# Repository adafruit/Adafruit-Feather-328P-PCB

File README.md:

## Adafruit Feather 328P PCB

<a href="http://www.adafruit.com/products/3458"><br/>
Click here to purchase one from the Adafruit shop</a>

PCB files for the Adafruit Feather 328P. Format is EagleCAD schematic and board layout

For more details, check out the product page at
* https://www.adafruit.com/product/3458

### Description

With this Feather we're getting a little nostalgic for the ATmega328P - the classic 'Arduino' chip - with this Adafruit Feather 328P running a 3.3V and 8 MHz. Feather is the new development board from Adafruit, and like it's namesake it is thin, light, and lets you fly! We designed Feather to be a new standard for portable microcontroller cores. We have other boards in the Feather family, check'em out here.

At the Feather 328P's heart is an ATmega328P clocked at 8 MHz and at 3.3V logic, a chip setup we've had tons of experience with as it's the same as the Pro Mini and similar to the Adafruit Metro 328. This chip has 32K of flash and 2K of RAM, and we paired it with a SiLabs CP2104 to give it USB-to-Serial program & debug capability built in. Works great when you want to keep your classic Arduino code compatibility, but want to use one of our dozens of FeatherWings

To make it easy to use for portable projects, we added a connector for any of our 3.7V Lithium polymer batteries and built in battery charging. You don't need a battery, it will run just fine straight from the micro USB connector. But, if you do have a battery, you can take it on the go, then plug in the USB to recharge. The Feather will automatically switch over to USB power when its available. We also tied the battery thru a divider to an analog pin, so you can measure and monitor the battery voltage to detect when you need a recharge.

### License

Adafruit invests time and resources providing this open source design, please support Adafruit and open-source hardware by purchasing products from [Adafruit](https://www.adafruit.com)!

Designed by Limor Fried/Ladyada for Adafruit Industries.

Creative Commons Attribution/Share-Alike, all text above must be included in any redistribution. See license.txt for additional details.

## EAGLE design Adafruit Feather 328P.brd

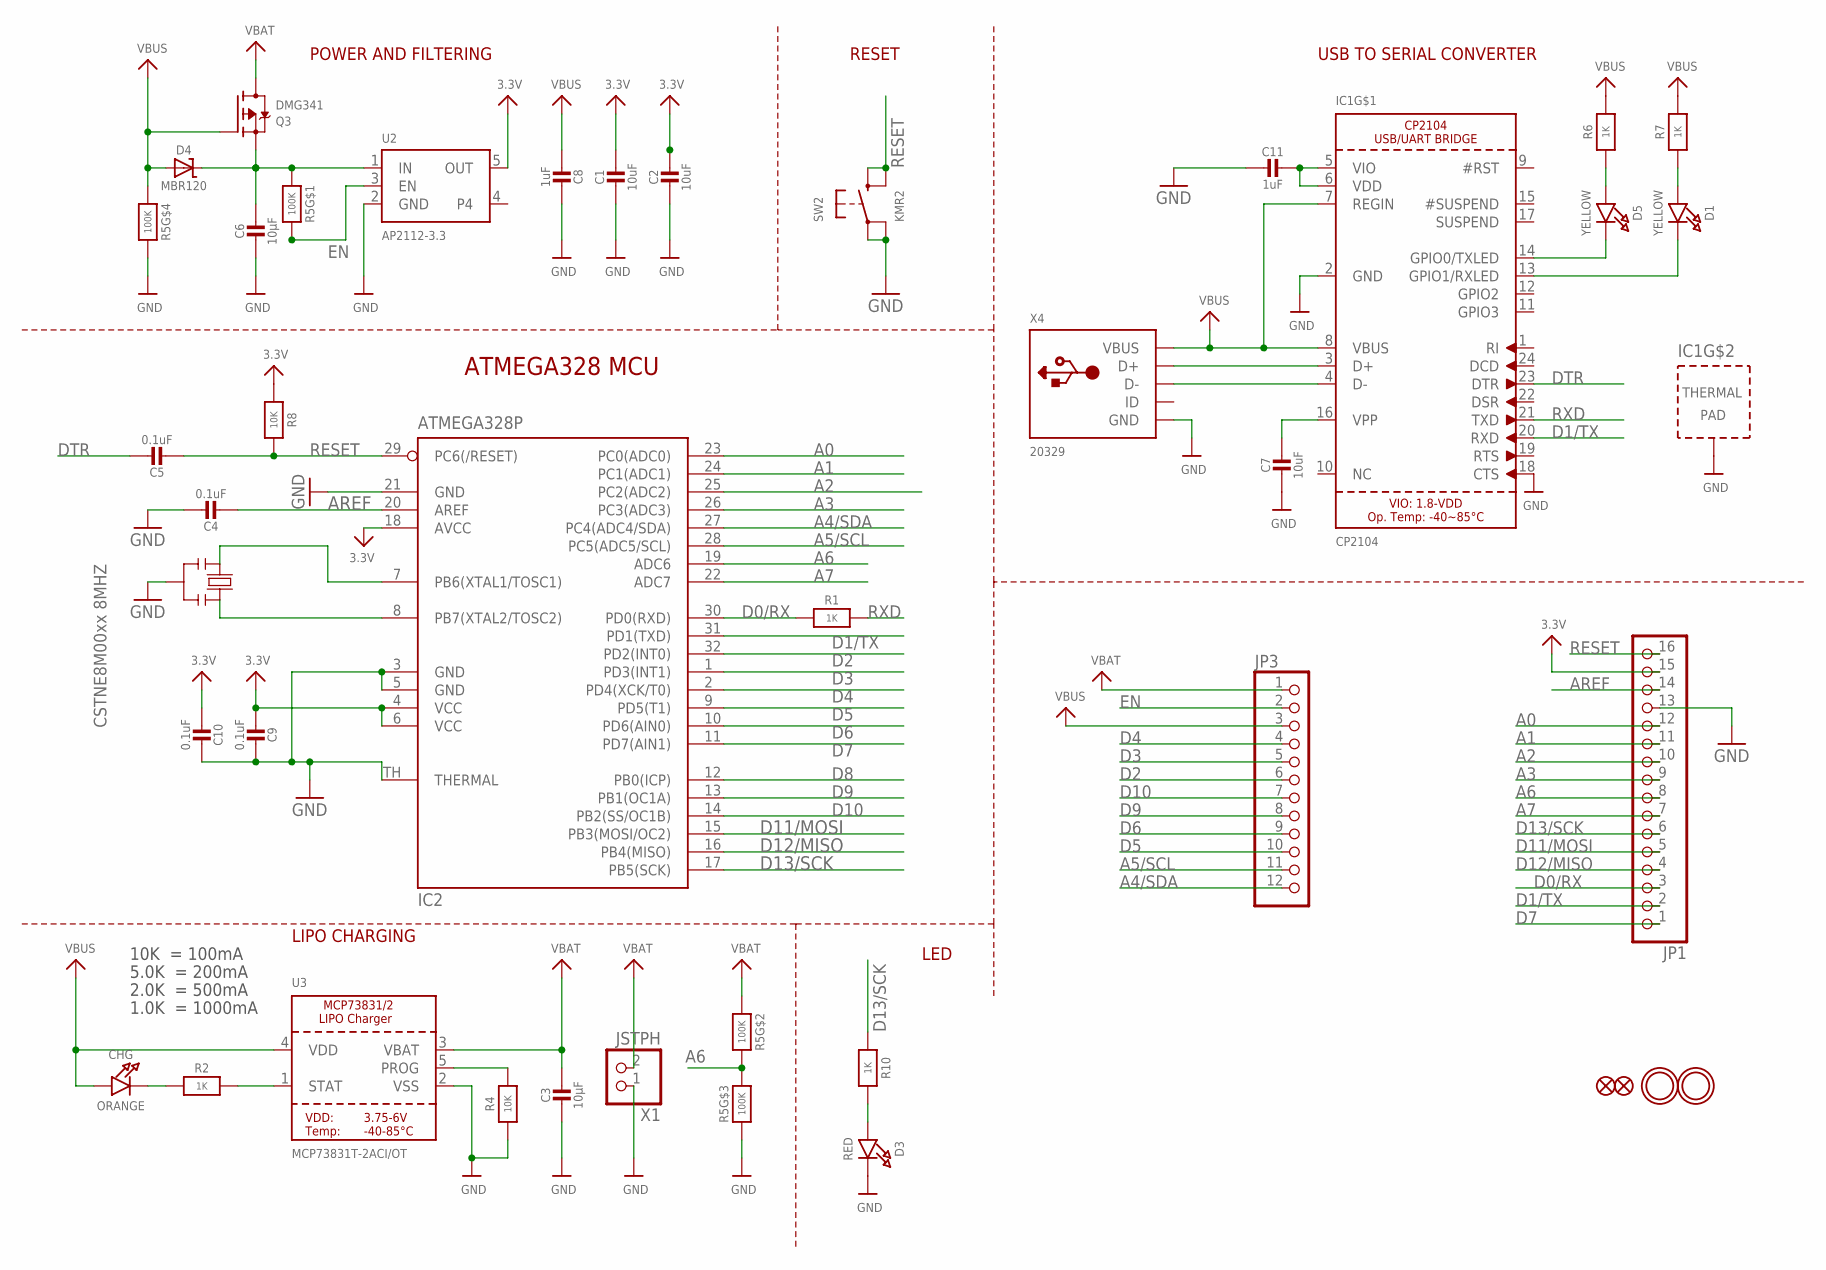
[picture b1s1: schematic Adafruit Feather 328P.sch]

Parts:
C1, C2: 10uF; 0805-NO
C3, C6: 10µF; 0805-NO
C4, C5, C9, C10: 0.1uF; 0603-NO
C7: 10uF; _0805MP
C8, C11: 1uF; 0603-NO
CHG: ORANGE; CHIPLED_0805_NOOUTLINE
D1, D5: YELLOW; CHIPLED_0805_NOOUTLINE
D3: RED; CHIPLED_0805_NOOUTLINE
D4: MBR120; SOD-123
IC1: CP2104; QFN24_4MM_SMSC
IC2: ATMEGA328P; MLF32-TH
JP1: HEADER-1X16ROUND; 1X16_ROUND
JP3: HEADER-1X12; 1X12_ROUND
Q3: DMG341; SOT23-R
R1: 1K; _0603MP
R2, R6, R7, R10: 1K; 0603-NO
R4, R8: 10K; 0603-NO
R5: 100K; RESPACK_4X0603
SW2: KMR2; BTN_KMR2_4.6X2.8
U2: AP2112-3.3; SOT23-5
U3: MCP73831T-2ACI/OT; SOT23-5
U$31, U$32: MOUNTINGHOLE2.5; MOUNTINGHOLE_2.5_PLATED
U$34, U$35: FIDUCIAL_1MM
X1: JSTPH; JSTPH2
X4: 20329; 4UCONN_20329_V2
Y2: CSTNE8M00xx 8MHZ; RESONATOR

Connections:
3.3V: C1.1, C2.1, C9.2, C10.2, IC2.4 (VCC), IC2.6 (VCC), IC2.18 (AVCC), JP1.15, R8.2, U2.5 (OUT)
A0: IC2.23 (PC0(ADC0)), JP1.12
A1: IC2.24 (PC1(ADC1)), JP1.11
A2: IC2.25 (PC2(ADC2)), JP1.10
A3: IC2.26 (PC3(ADC3)), JP1.9
A4/SDA: IC2.27 (PC4(ADC4/SDA)), JP3.12
A5/SCL: IC2.28 (PC5(ADC5/SCL)), JP3.11
A6: IC2.19 (ADC6), JP1.8, R5.6 (2), R5.7 (2)
A7: IC2.22 (ADC7), JP1.7
AREF: C4.2, IC2.20 (AREF), JP1.14
D0/RX: IC2.30 (PD0(RXD)), JP1.3, R1.1
D1/TX: IC1.20 (RXD), IC2.31 (PD1(TXD)), JP1.2
D2: IC2.32 (PD2(INT0)), JP3.6
D3: IC2.1 (PD3(INT1)), JP3.5
D4: IC2.2 (PD4(XCK/T0)), JP3.4
D5: IC2.9 (PD5(T1)), JP3.10
D6: IC2.10 (PD6(AIN0)), JP3.9
D7: IC2.11 (PD7(AIN1)), JP1.1
D8: IC2.12 (PB0(ICP))
D9: IC2.13 (PB1(OC1A)), JP3.8
D10: IC2.14 (PB2(SS/OC1B)), JP3.7
D11/MOSI: IC2.15 (PB3(MOSI/OC2)), JP1.5
D12/MISO: IC2.16 (PB4(MISO)), JP1.4
D13/SCK: IC2.17 (PB5(SCK)), JP1.6, R10.1
DTR: C5.1, IC1.23 (DTR)
EN: JP3.2, R5.8 (2), U2.3 (EN)
GND: C1.2, C2.2, C3.2, C4.1, C6.2, C7.2, C8.1, C9.1, C10.1, C11.2, D3.C, IC1.2 (GND), IC1.18 (CTS), IC1.THERM (TP), IC2.3 (GND), IC2.5 (GND), IC2.21 (GND), IC2.TH (THERMAL), JP1.13, R4.1, R5.3 (1), R5.5 (2), SW2.A, SW2.A' (P1), U2.2 (GND), U3.2 (VSS), X1.1, X4.BASE@1 (GND), X4.BASE@2 (GND), X4.GND, X4.SPRT@1 (GND), X4.SPRT@2 (GND), X4.SPRT@3 (GND), X4.SPRT@4 (GND), Y2.2
unnamed: CHG.C, R2.1
unnamed: IC1.3 (D+), X4.D+
unnamed: R2.2, U3.1 (STAT)
unnamed: R4.2, U3.5 (PROG)
unnamed: D3.A, R10.2
unnamed: IC1.4 (D-), X4.D-
unnamed: C6.1, D4.C, Q3.2 (S), R5.1, U2.1 (IN)
unnamed: D1.A, R7.1
unnamed: D5.A, R6.1
unnamed: C11.1, IC1.5 (VIO), IC1.6 (VDD)
unnamed: C7.1, IC1.16 (VPP)
RESET: C5.2, IC2.29 (PC6(/RESET)), JP1.16, R8.1, SW2.B (S), SW2.B' (S1)
RXD: IC1.21 (TXD), R1.2
RXLED: D1.C, IC1.13 (GPIO1/RXLED)
TXLED: D5.C, IC1.14 (GPIO0/TXLED)
VBAT: C3.1, JP3.1, Q3.3 (D), R5.2 (1), U3.3 (VBAT), X1.2
VBUS: C8.2, CHG.A, D4.A, IC1.7 (REGIN), IC1.8 (VBUS), JP3.3, Q3.1 (G), R5.4 (1), R6.2, R7.2, U3.4 (VDD), X4.VBUS
XTAL1: IC2.8 (PB7(XTAL2/TOSC2)), Y2.3
XTAL2: IC2.7 (PB6(XTAL1/TOSC1)), Y2.1

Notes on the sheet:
POWER AND FILTERING
RESET
10K = 100mA
5.0K = 200mA
2.0K = 500mA
1.0K = 1000mA
USB TO SERIAL CONVERTER
LIPO CHARGING
LED
ATMEGA328 MCU

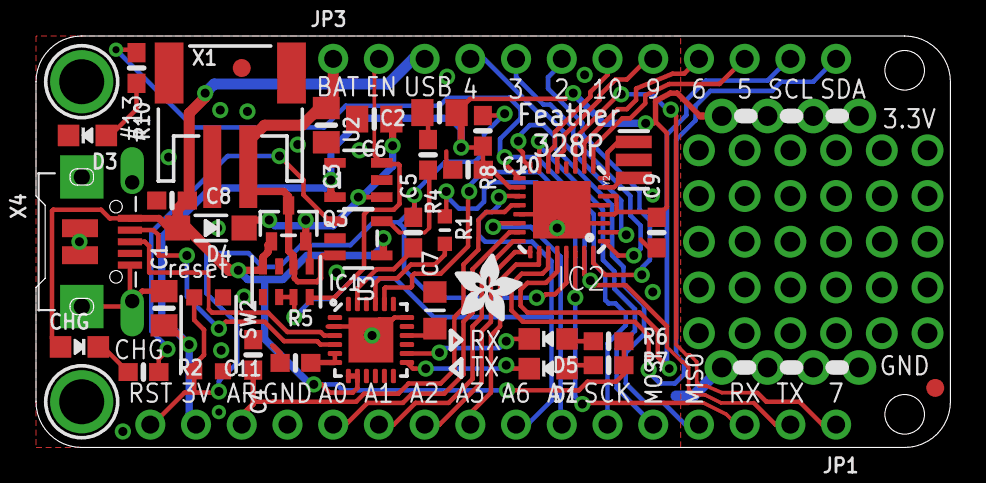
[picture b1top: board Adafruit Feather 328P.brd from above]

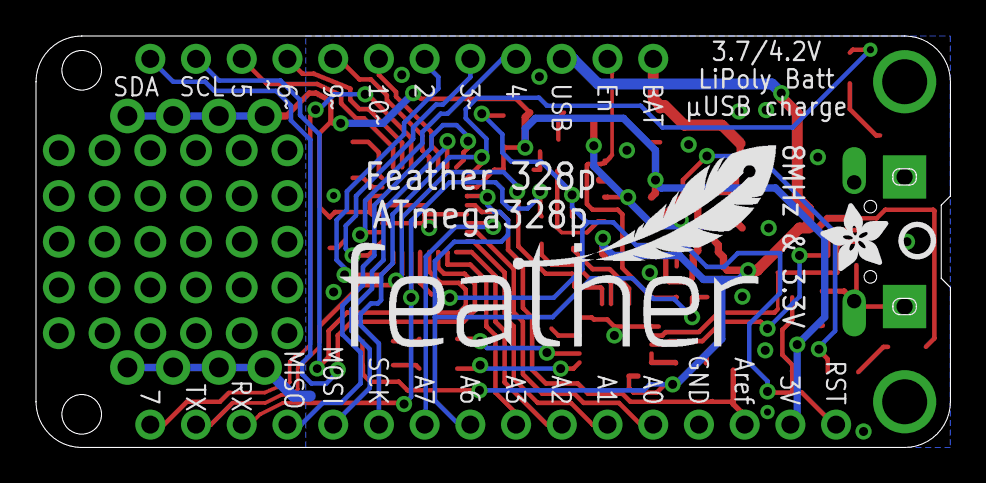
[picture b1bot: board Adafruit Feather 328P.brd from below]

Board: 2 copper layers, 50.8 x 22.9 mm, 43 parts (3 on the bottom side), 45 nets.

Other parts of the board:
U$9: FEATHERLOGO
U$13: PCBFEAT-REV-040
U$15, U$44: ADAFRUIT_3.5MM

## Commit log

2018-01-24 init
2020-10-17 fix https://github.com/adafruit/Adafruit-Feather-328P-PCB/issues/2
2022-04-05 Added prettypins

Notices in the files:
parts and their libraries:
microbuilder: This work is placed in the public domain, and may be freely used for commercial and non-commercial work with the following conditions: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
